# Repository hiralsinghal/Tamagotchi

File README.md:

# Tamagotchi

This is a Tamagotchi. It is a small handheld video game in which you have a pet. You can play with it, feed it and more depending on your firmware code.

## Features

- Play with the pet!
- Feed it!
- Make it sleep!

You can always customise the firmware to make it do what you want!

## Schematic

Here's the schematic for the Tamagotchi. It has XIAO-ESP32-C3-SMD as its MCU. It has an OLED display, a buzzer, 4 switches and a battery cell.

## PCB

Its a pentagon shaped PCB, which has stars on it silkscreen.

## Case

I made the case using Fusion. It has stars on the top case (goes with the PCB).

The source file is in the folder CAD.

## BOM

Here you can find the [BOM](BOM.csv)!

## Zine

## Why did I make it?

I made it for Fallout. Making this improved my electronics skills. I now know that I should read datasheets to understand how a pin on a component works. Because of this, I had to work on CAD which are now a lot better than before.

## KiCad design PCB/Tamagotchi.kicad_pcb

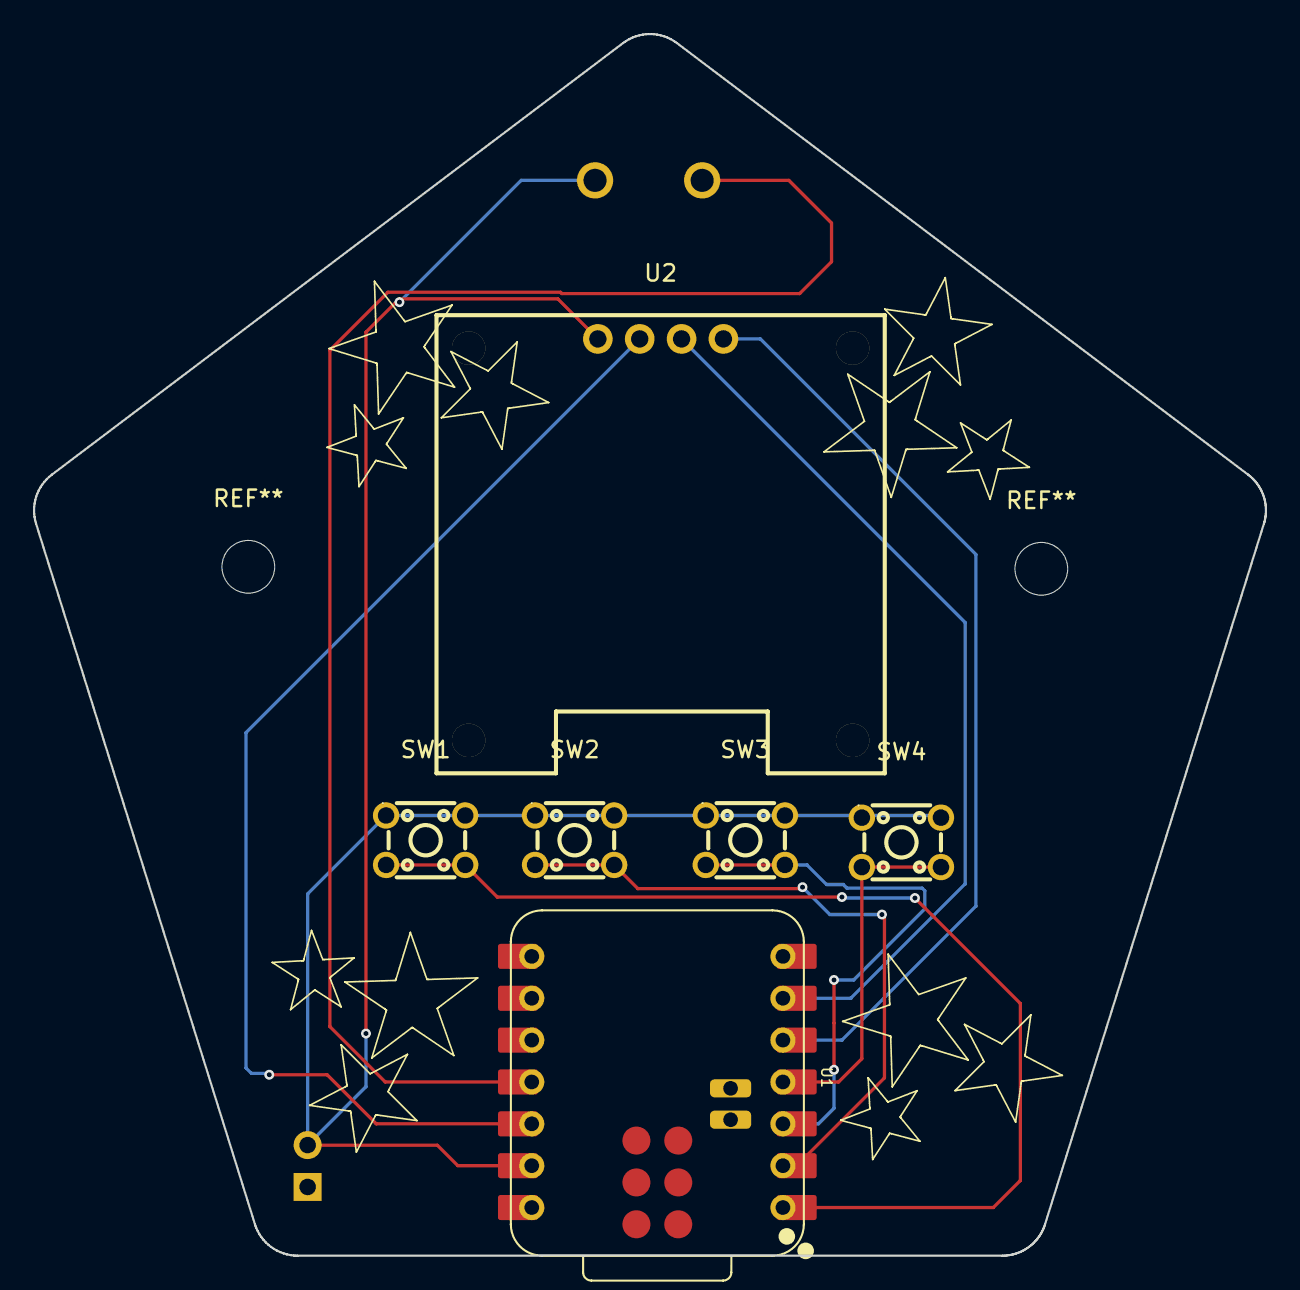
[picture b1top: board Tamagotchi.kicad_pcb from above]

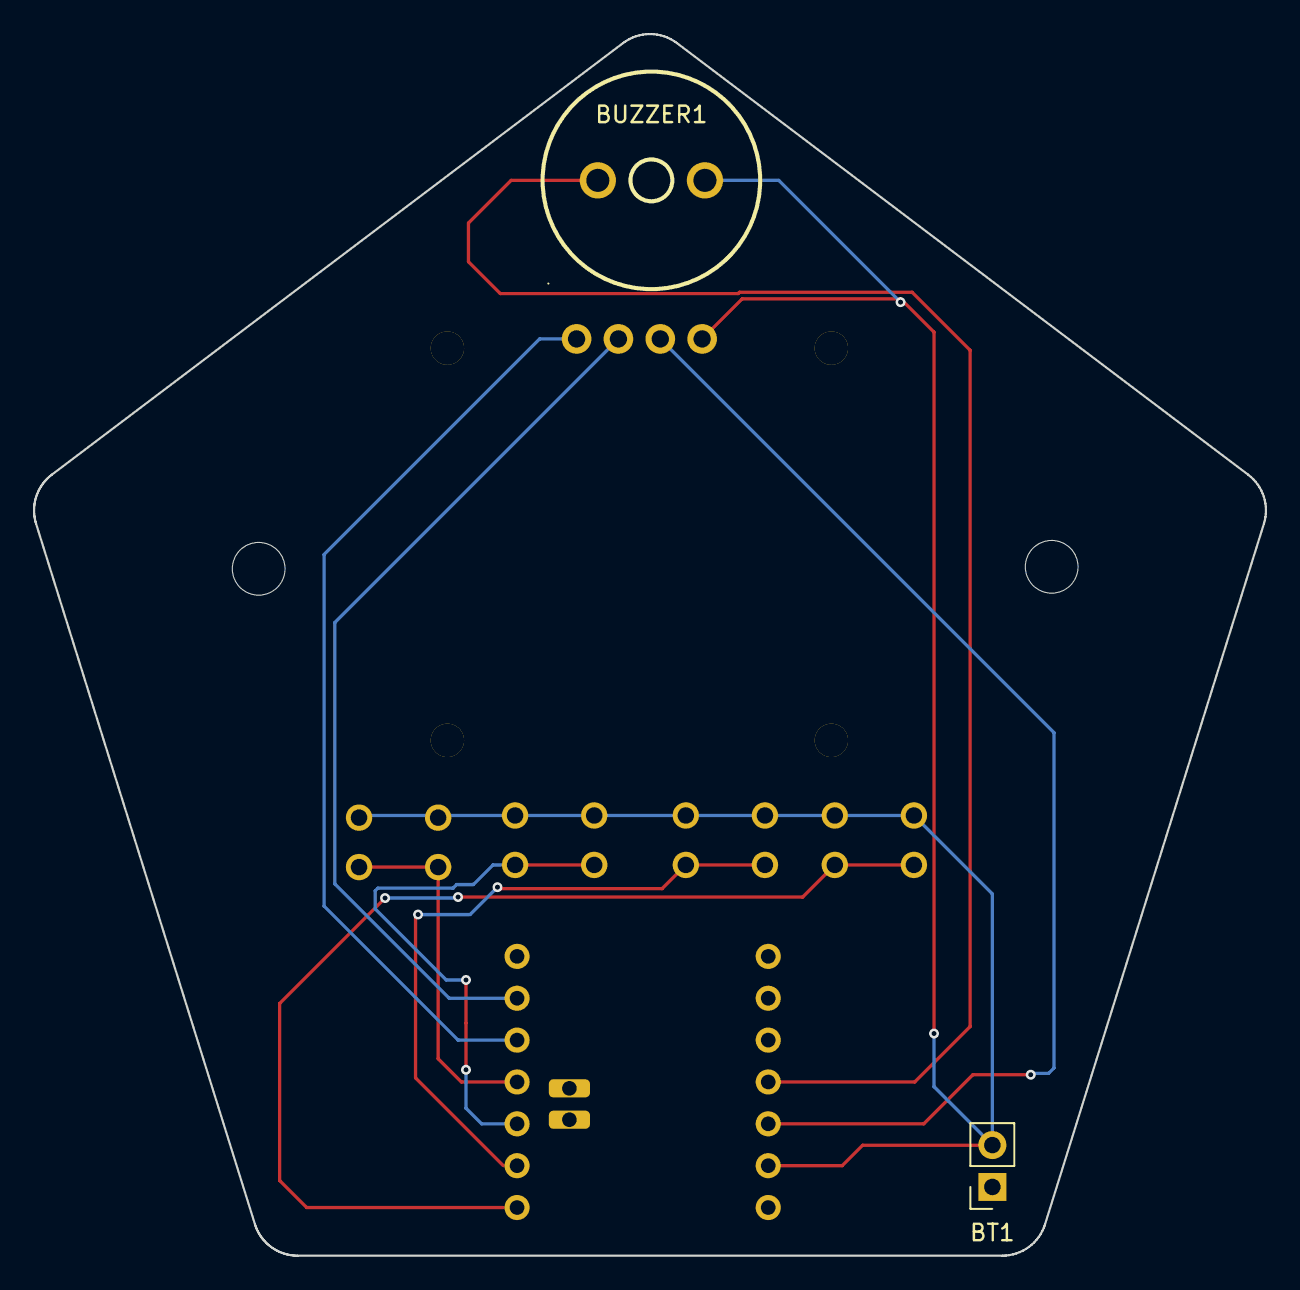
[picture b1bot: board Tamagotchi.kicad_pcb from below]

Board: 2 copper layers, 74.8 x 74.1 mm, 8 parts (2 on the bottom side), 9 nets.

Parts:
BT1: Battery_Cell; PinSocket_1x02_P2.54mm_Vertical
BUZZER1: 1207-P6.5MM; BUZ-TH_BD12.5-P6.50-D1.4
SW1, SW2, SW3, SW4: SW_Push; SW-TH_4P-L4.5-W4.5-P3.00-LS4.8
U1: XIAO-ESP32-C3-SMD; XIAO-ESP32-C3-DIP-SMD
U2: HS96L03W2C03; OLED-TH_L27.8-W27.2-P2.54_C9900033791

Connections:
+3V3: U1.12 (3V3), U2.2 (VCC)
GND: BT1.2 (-), BUZZER1.2 (-), SW1.1, SW2.1, SW3.1, SW4.1, U1.13 (GND), U2.1 (GND)
unnamed: BUZZER1.1 (+), U1.11 (GPIO10_D10_MOSI)
unnamed: SW1.2, U1.1 (GPIO2_A0_D0)
unnamed: SW2.2, U1.2 (GPIO3_A1_D1)
unnamed: SW3.2, U1.3 (GPIO4_A2_D2)
unnamed: SW4.2, U1.4 (GPIO5_A3_D3)
unnamed: U1.5 (GPIO6_D4_SDA), U2.4 (SDA)
unnamed: U1.6 (GPIO7_D5_SCL), U2.3 (SCL)

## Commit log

2026-05-24 readme
2026-05-31 PCB folder done
2026-05-31 aseets
2026-05-31 production & firmware
2026-05-31 and m almost done
2026-05-31 done
2026-06-05 CAD new files
2026-06-05 new cad files for production
2026-06-05 new case pic
2026-06-05 updated zine
2026-06-05 update bom
2026-06-05 bom update
2026-06-08 fixing step 1
2026-06-08 fixing step 2
2026-06-08 fixing
2026-06-08 updated bom
2026-06-08 pls work
2026-06-08 i hope it works now
2026-06-08 added pic
2026-06-09 new cad files
2026-06-09 zine update
2026-06-09 readme update
2026-06-09 update case pic
2026-06-09 Rename tamagotchi.png to tamagotchi-case.png
2026-06-09 Update image reference for Tamagotchi case
2026-06-09 file changed in production
